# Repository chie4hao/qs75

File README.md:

# qs75
A 15x5 full-grid othorlinear keyboard

## Features

* STM32 ARM MCU
* QMK firmware compatible
* Per-switch RGB LED
* Kailh's hot-swappable MX sockets
* USB type-c
* Compatible with universal 60% cases
* Fully open-source

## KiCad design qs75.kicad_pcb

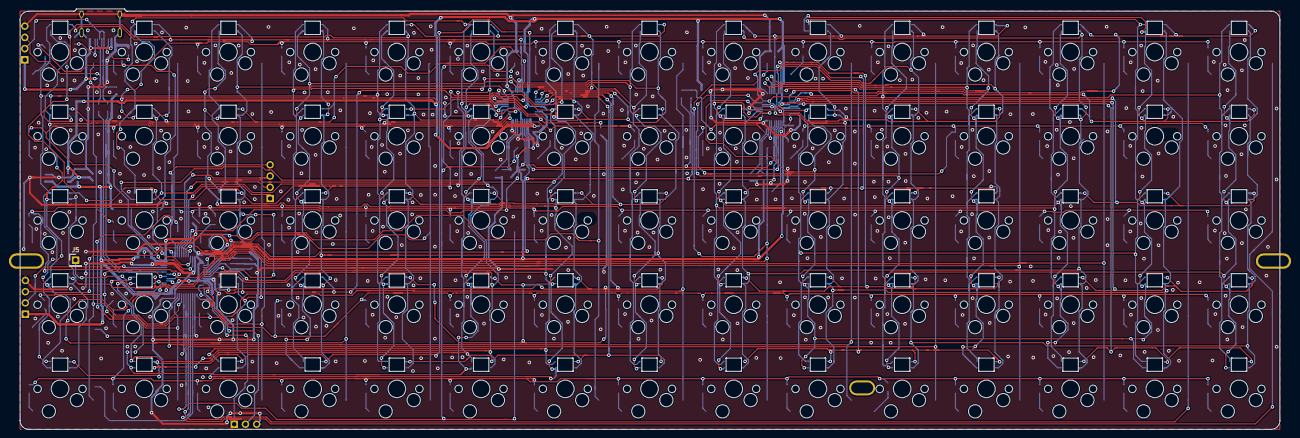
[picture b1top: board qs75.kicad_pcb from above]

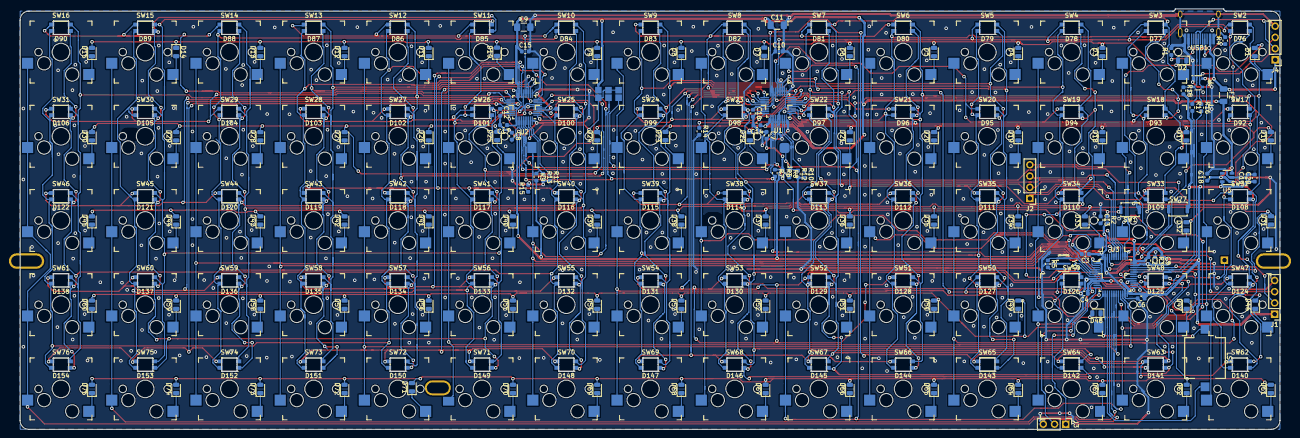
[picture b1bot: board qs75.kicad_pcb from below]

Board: 2 copper layers, 285.0 x 95.1 mm, 287 parts (205 on the bottom side), 174 nets.

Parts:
C2, C3, C4, C13, C19: 104; C_0603_1608Metric
C5, C6, C18, C20: 106; C_0603_1608Metric
C7, C8, C10, C12, C14, C15, C16, C17: 0.1uF; C_0603_1608Metric
C9, C11: 22uF/10V; C_1206_3216Metric_Pad1.42x1.75mm_HandSolder
D1, D2, D3, D4, D5, D6, D7, D8, D9, D10, D11, D12, D13, D14, D15, D16, D17, D18, D19, D20, D21, D22, D23, D24, D25, D26, D27, D28, D29, D30, D31, D32, D33, D34, D35, D36, D37, D38, D39, D40, D41, D42, D43, D44, D45, D46, D47, D48, D49, D50, D51, D52, D53, D54, D55, D56, D57, D58, D59, D60, D61, D62, D63, D64, D65, D66, D67, D68, D69, D70, D71, D72, D73, D74, D75: 1N4148; D_0805_2012Metric
D76, D77, D78, D79, D80, D81, D82, D83, D84, D85, D86, D87, D88, D89, D90, D92, D93, D94, D95, D96, D97, D98, D99, D100, D101, D102, D103, D104, D105, D106, D108, D109, D110, D111, D112, D113, D114, D115, D116, D117, D118, D119, D120, D121, D122, D124, D125, D126, D127, D128, D129, D130, D131, D132, D133, D134, D135, D136, D137, D138, D140, D141, D142, D143, D144, D145, D146, D147, D148, D149, D150, D151, D152, D153, D154: LED_RABG; LED_Kingbright_AAA3528ESGCT
F1: 2A; Fuse_1206_3216Metric
HOLE: VAL**; PKRH
HOLE#2: VAL**; PKRHC
HOLE#3, HOLE#5: VAL**; PKRH
HOLE#4, HOLE#6: VAL**; PKRHSL
J1: SWD; PinHeader_1x04_P2.54mm_Vertical
J2: SPI; PinHeader_1x04_P2.54mm_Vertical
J3: UART; PinHeader_1x03_P2.54mm_Vertical
J4: USB2.0; PinHeader_1x04_P2.54mm_Vertical
J5: PB14; PinHeader_1x01_P2.54mm_Vertical
JP1, JP3, JP4: Jumper_NO_Small; Jumper-UserFriendly-Small
LS1: Speaker; Buzzer_CUI_CPT-9019S-SMT
R1, R4: 5.1k; R_0603_1608Metric
R2, R3: 10k; R_0603_1608Metric
R5: 1M; R_0603_1608Metric
R6, R7: 1k; R_0603_1608Metric
R8, R9: NC; R_0603_1608Metric
R10, R11, R12, R13: 100k; R_0603_1608Metric
R14, R15: 20k; R_0603_1608Metric
R16, R17: 22; R_0603_1608Metric
R18: 1.5k; R_0603_1608Metric
SW1, SW77: SW_Push; SW_Push_SPST_NO_Alps_SKRK
SW2, SW3, SW4, SW5, SW6, SW7, SW8, SW9, SW10, SW11, SW12, SW13, SW14, SW15, SW16, SW17, SW18, SW19, SW20, SW21, SW22, SW23, SW24, SW25, SW26, SW27, SW28, SW29, SW30, SW31, SW32, SW33, SW34, SW35, SW36, SW37, SW38, SW39, SW40, SW41, SW42, SW43, SW44, SW45, SW46, SW47, SW48, SW49, SW50, SW51, SW52, SW53, SW54, SW55, SW56, SW57, SW58, SW59, SW60, SW61, SW62, SW63, SW64, SW65, SW66, SW67, SW68, SW69, SW70, SW71, SW72, SW73, SW74, SW75, SW76: 1u; Kailh_socket
U1, U2: IS31FL3737; qfn-40-5x5mm
U3: STM32F303CCTx; LQFP-48_7x7mm_P0.5mm
U4: PRTR5V0U2X; SOT-143B
U5: XC6220B331MR; SOT-23-5
USB1: HRO-TYPE-C-31-M-12; HRO-TYPE-C-31-M-12-HandSoldering
Y1: 8M; Resonator_SMD_muRata_CSTxExxV-3Pin_3.0x1.1mm_HandSoldering

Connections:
+3V3: C2.1, C3.1, C4.1, C5.1, C6.1, C7.2, C8.2, C19.1, C20.1, J1.1, R2.2, R6.1, R7.1, R8.2, R9.2, R18.2, SW77.2, U1.32, U2.32, U3.1, U3.9, U3.24, U3.36, U3.48, U5.5
+5V: C9.1, C10.1, C11.1, C12.1, C14.1, C15.1, C16.1, C17.1, C18.1, F1.2, JP1.1, U1.19, U1.26, U1.31, U2.19, U2.26, U2.31, U5.1, U5.3
COL0: SW2.2, SW17.2, SW32.2, SW47.2, SW62.2, U3.20
COL1: SW3.2, SW18.2, SW33.2, SW48.2, SW63.2, U3.21
COL2: SW4.2, SW19.2, SW34.2, SW49.2, SW64.2, U3.11
COL3: SW5.2, SW20.2, SW35.2, SW50.2, SW65.2, U3.26
COL4: SW6.2, SW21.2, SW36.2, SW51.2, SW66.2, U3.4
COL5: SW7.2, SW22.2, SW37.2, SW52.2, SW67.2, U3.18
COL6: SW8.2, SW23.2, SW38.2, SW53.2, SW68.2, U3.3
COL7: SW9.2, SW24.2, SW39.2, SW54.2, SW69.2, U3.10
COL8: SW10.2, SW25.2, SW40.2, SW55.2, SW70.2, U3.2
COL9: SW11.2, SW26.2, SW41.2, SW56.2, SW71.2, U3.22
COL10: SW12.2, SW27.2, SW42.2, SW57.2, SW72.2, U3.19
COL11: SW13.2, SW28.2, SW43.2, SW58.2, SW73.2, U3.28
COL12: SW14.2, SW29.2, SW44.2, SW59.2, SW74.2, U3.31
COL13: SW15.2, SW30.2, SW45.2, SW60.2, SW75.2, U3.17
COL14: SW16.2, SW31.2, SW46.2, SW61.2, SW76.2, U3.16
GND: C2.2, C3.2, C4.2, C5.2, C6.2, C7.1, C8.1, C9.2, C10.2, C11.2, C12.2, C13.1, C14.2, C15.2, C16.2, C17.2, C18.2, C19.2, C20.2, J1.4, J3.3, J4.4, R1.2, R3.2, R4.2, R10.2, R11.2, R12.2, R13.2, R14.2, R15.2, SW1.1, U1.4, U1.11, U1.29, U1.36, U1.40, U2.4, U2.11, U2.29, U2.40, U3.8, U3.23, U3.35, U3.47, U4.1, U5.2, USB1.1, USB1.12, USB1.13, Y1.2
MISO: J2.2, U3.40
MOSI: J2.1, U3.41
NSS: J2.4, U3.38
unnamed: C13.2, R2.1, SW1.2, U3.7
unnamed: D1.1, SW2.1
unnamed: D2.1, SW3.1
unnamed: D3.1, SW4.1
unnamed: D4.1, SW5.1
unnamed: D5.1, SW6.1
unnamed: D6.1, SW7.1
unnamed: D7.1, SW8.1
unnamed: D8.1, SW9.1
unnamed: D9.1, SW10.1
unnamed: D10.1, SW11.1
unnamed: D11.1, SW12.1
unnamed: D12.1, SW13.1
unnamed: D13.1, SW14.1
unnamed: D14.2, SW15.1
unnamed: D15.1, SW16.1
unnamed: D16.1, SW17.1
unnamed: D17.1, SW18.1
unnamed: D18.1, SW19.1
unnamed: D19.1, SW20.1
unnamed: D20.1, SW21.1
unnamed: D21.1, SW22.1
unnamed: D22.1, SW23.1
unnamed: D23.1, SW24.1
unnamed: D24.1, SW25.1
unnamed: D25.1, SW26.1
unnamed: D26.1, SW27.1
unnamed: D27.1, SW28.1
unnamed: D28.1, SW29.1
unnamed: D29.1, SW30.1
unnamed: D30.1, SW31.1
unnamed: D31.1, SW32.1
unnamed: D32.1, SW33.1
unnamed: D33.1, SW34.1
unnamed: D34.1, SW35.1
unnamed: D35.1, SW36.1
unnamed: D36.1, SW37.1
unnamed: D37.1, SW38.1
unnamed: D38.1, SW39.1
unnamed: D39.1, SW40.1
unnamed: D40.1, SW41.1
unnamed: D41.1, SW42.1
unnamed: D42.1, SW43.1
unnamed: D43.1, SW44.1
unnamed: D44.1, SW45.1
unnamed: D45.1, SW46.1
unnamed: D46.1, SW47.1
unnamed: D47.1, SW48.1
unnamed: D48.1, SW49.1
unnamed: D49.1, SW50.1
unnamed: D50.1, SW51.1
unnamed: D51.1, SW52.1
unnamed: D52.1, SW53.1
unnamed: D53.1, SW54.1
unnamed: D54.1, SW55.1
unnamed: D55.1, SW56.1
unnamed: D56.1, SW57.1
unnamed: D57.1, SW58.1
unnamed: D58.1, SW59.1
unnamed: D59.1, SW60.1
unnamed: D60.1, SW61.1
unnamed: D61.1, SW62.1
unnamed: D62.1, SW63.1
unnamed: D63.1, SW64.1
unnamed: D64.1, SW65.1
unnamed: D65.1, SW66.1
unnamed: D66.1, SW67.1
unnamed: D67.1, SW68.1
unnamed: D68.1, SW69.1
unnamed: D69.1, SW70.1
unnamed: D70.1, SW71.1
unnamed: D71.1, SW72.1
unnamed: D72.1, SW73.1
unnamed: D73.1, SW74.1
unnamed: D74.1, SW75.1
unnamed: D75.1, SW76.1
unnamed: J5.1, U3.27
unnamed: JP1.2, JP3.2, JP4.2, U2.36
unnamed: R1.1, USB1.10
unnamed: R3.1, SW77.1, U3.44
unnamed: R4.1, USB1.4
unnamed: R5.1, U3.5, Y1.1
unnamed: R5.2, U3.6, Y1.3
unnamed: R10.1, U1.39
unnamed: R11.1, U2.39
unnamed: R8.1, R12.1, U1.38
unnamed: R9.1, R13.1, U2.38
unnamed: R14.1, U1.30
unnamed: R15.1, U2.30
unnamed: R16.2, U3.32
unnamed: R17.2, U3.33
unnamed: U1.33, U2.33
PA4: LS1.1, U3.14
PA5: LS1.2, U3.15
ROW0: D1.2, D2.2, D3.2, D4.2, D5.2, D6.2, D7.2, D8.2, D9.2, D10.2, D11.2, D12.2, D13.2, D14.1, D15.2, U3.45
ROW1: D16.2, D17.2, D18.2, D19.2, D20.2, D21.2, D22.2, D23.2, D24.2, D25.2, D26.2, D27.2, D28.2, D29.2, D30.2, U3.46
ROW2: D31.2, D32.2, D33.2, D34.2, D35.2, D36.2, D37.2, D38.2, D39.2, D40.2, D41.2, D42.2, D43.2, D44.2, D45.2, U3.29
ROW3: D46.2, D47.2, D48.2, D49.2, D50.2, D51.2, D52.2, D53.2, D54.2, D55.2, D56.2, D57.2, D58.2, D59.2, D60.2, U3.30
ROW4: D61.2, D62.2, D63.2, D64.2, D65.2, D66.2, D67.2, D68.2, D69.2, D70.2, D71.2, D72.2, D73.2, D74.2, D75.2, U3.25
RXD: J3.1, U3.13
SCK: J2.3, U3.39
SCL: JP4.1, R6.2, U1.35, U2.35, U3.42
SDA: JP3.1, R7.2, U1.34, U2.34, U3.43
SWCLK: J1.3, U3.37
SWDIO: J1.2, U3.34
TXD: J3.2, U3.12
USB_D+: J4.2, R17.1, R18.1, U4.2, USB1.6, USB1.8
USB_D-: J4.3, R16.1, U4.3, USB1.5, USB1.7
VCC: F1.1, J4.1, U4.4, USB1.2, USB1.11
aCS1: D76.2, D77.2, D78.2, D79.2, U1.15
aCS2: D92.2, D93.2, D94.2, D95.2, U1.16
aCS3: D108.2, D109.2, D110.2, D111.2, U1.17
aCS4: D124.2, D125.2, D126.2, D127.2, U1.18
aCS5: D140.2, D141.2, D142.2, D143.2, U1.20
aCS6: D80.2, D81.2, D82.2, D83.2, U1.21
aCS7: D96.2, D97.2, D98.2, D99.2, U1.22
aCS8: D112.2, D113.2, D114.2, D115.2, U1.23
aCS9: D128.2, D129.2, D130.2, D131.2, U1.24
aCS10: D144.2, D145.2, D146.2, D147.2, U1.25
aSW1: D76.1, D80.1, D92.1, D96.1, D108.1, D112.1, D124.1, D128.1, D140.1, D144.1, U1.1
aSW2: D76.4, D80.4, D92.4, D96.4, D108.4, D112.4, D124.4, D128.4, D140.4, D144.4, U1.2
aSW3: D76.3, D80.3, D92.3, D96.3, D108.3, D112.3, D124.3, D128.3, D140.3, D144.3, U1.3
aSW4: D77.1, D81.1, D93.1, D97.1, D109.1, D113.1, D125.1, D129.1, D141.1, D145.1, U1.5
aSW5: D77.4, D81.4, D93.4, D97.4, D109.4, D113.4, D125.4, D129.4, D141.4, D145.4, U1.6
aSW6: D77.3, D81.3, D93.3, D97.3, D109.3, D113.3, D125.3, D129.3, D141.3, D145.3, U1.7
aSW7: D78.1, D82.1, D94.1, D98.1, D110.1, D114.1, D126.1, D130.1, D142.1, D146.1, U1.8
aSW8: D78.4, D82.4, D94.4, D98.4, D110.4, D114.4, D126.4, D130.4, D142.4, D146.4, U1.9
aSW9: D78.3, D82.3, D94.3, D98.3, D110.3, D114.3, D126.3, D130.3, D142.3, D146.3, U1.10
aSW10: D79.1, D83.1, D95.1, D99.1, D111.1, D115.1, D127.1, D131.1, D143.1, D147.1, U1.12
aSW11: D79.4, D83.4, D95.4, D99.4, D111.4, D115.4, D127.4, D131.4, D143.4, D147.4, U1.13
aSW12: D79.3, D83.3, D95.3, D99.3, D111.3, D115.3, D127.3, D131.3, D143.3, D147.3, U1.14
bCS1: D84.2, D85.2, D86.2, D87.2, U2.15
bCS2: D100.2, D101.2, D102.2, D103.2, U2.16
bCS3: D116.2, D117.2, D118.2, D119.2, U2.17
bCS4: D132.2, D133.2, D134.2, D135.2, U2.18
bCS5: D148.2, D149.2, D150.2, D151.2, U2.20
bCS6: D88.2, D89.2, D90.2, U2.21
bCS7: D104.2, D105.2, D106.2, U2.22
bCS8: D120.2, D121.2, D122.2, U2.23
bCS9: D136.2, D137.2, D138.2, U2.24
bCS10: D152.2, D153.2, D154.2, U2.25
bSW1: D84.1, D88.1, D100.1, D104.1, D116.1, D120.1, D132.1, D136.1, D148.1, D152.1, U2.1
bSW2: D84.4, D88.4, D100.4, D104.4, D116.4, D120.4, D132.4, D136.4, D148.4, D152.4, U2.2
bSW3: D84.3, D88.3, D100.3, D104.3, D116.3, D120.3, D132.3, D136.3, D148.3, D152.3, U2.3
bSW4: D85.1, D89.1, D101.1, D105.1, D117.1, D121.1, D133.1, D137.1, D149.1, D153.1, U2.5
bSW5: D85.4, D89.4, D101.4, D105.4, D117.4, D121.4, D133.4, D137.4, D149.4, D153.4, U2.6
bSW6: D85.3, D89.3, D101.3, D105.3, D117.3, D121.3, D133.3, D137.3, D149.3, D153.3, U2.7
bSW7: D86.1, D90.1, D102.1, D106.1, D118.1, D122.1, D134.1, D138.1, D150.1, D154.1, U2.8
bSW8: D86.4, D90.4, D102.4, D106.4, D118.4, D122.4, D134.4, D138.4, D150.4, D154.4, U2.9
bSW9: D86.3, D90.3, D102.3, D106.3, D118.3, D122.3, D134.3, D138.3, D150.3, D154.3, U2.10
bSW10: D87.1, D103.1, D119.1, D135.1, D151.1, U2.12
bSW11: D87.4, D103.4, D119.4, D135.4, D151.4, U2.13
bSW12: D87.3, D103.3, D119.3, D135.3, D151.3, U2.14

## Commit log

2019-05-16 add kicad files
2019-05-16 Add submodules
2019-05-28 route tracks
2019-06-13 Change layout
2019-06-15 Reroute tracks
2019-06-16 Add tracks
2019-06-22 Add readme.md
2019-06-22 Modify readme
2019-07-01 Add holes for GH60-case
2019-07-01 Change README...
